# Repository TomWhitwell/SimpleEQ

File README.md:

# SimpleEQ  
Learn SMD soldering by building two channels of the kind of tone controls you’d find on an old hifi. 

Top channel = Baxandall EQ, treble/bass cut/boost   
Bottom channel = Tilt EQ  

No voltage control, but just enough range to push sounds into distortion. 

Works well in a feedback loop.

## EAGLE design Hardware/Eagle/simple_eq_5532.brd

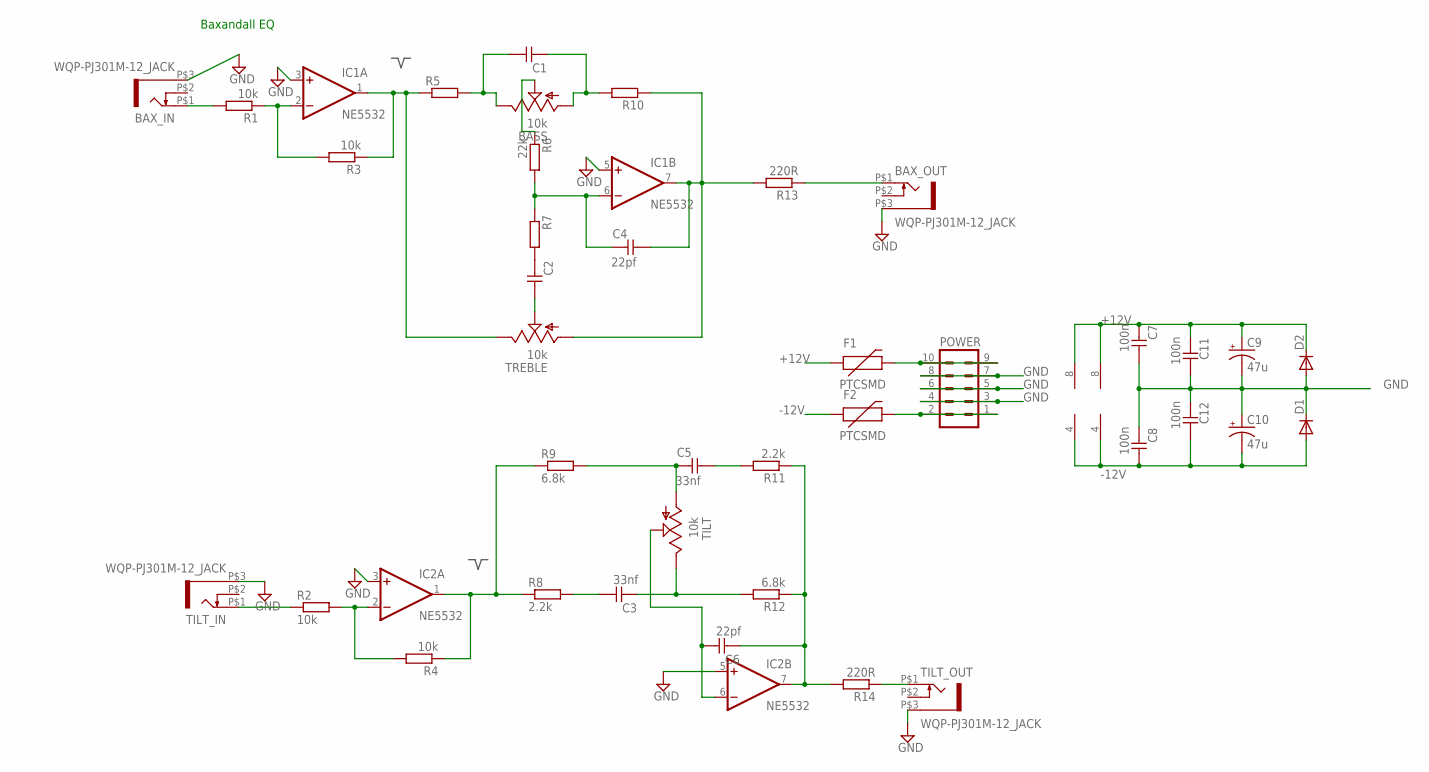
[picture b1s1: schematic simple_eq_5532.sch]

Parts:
BASS: 10k; EVUF
BAX_IN: WQP-PJ301M-12_JACK
BAX_OUT: WQP-PJ301M-12_JACK
C1, C2: C-EU0805_CAP; R0805
C3, C5: 33nf; R0805
C4, C6: 22pf; R0805
C7, C8, C11, C12: 100n; R0805
C9, C10: 47u; PANASONIC_D
D1, D2: DIODE-SOD123; SOD123
F1, F2: PTCSMD; PTC-1206
IC1, IC2: NE5532; SO08
POWER: 10_PIN_HEADER; MA05-2
R1, R2, R3, R4: 10k; R0805
R5, R7, R10: R-EU_R0805; R0805
R6: 22k; R0805
R8, R11: 2.2k; R0805
R9, R12: 6.8k; R0805
R13, R14: 220R; R0805
TILT: 10k; EVUF
TILT_IN: WQP-PJ301M-12_JACK
TILT_OUT: WQP-PJ301M-12_JACK
TREBLE: 10k; EVUF

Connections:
+12V: C7.2, C9.+, C11.2, D2.C, F1.1, IC1.8 (V+), IC2.8 (V+)
-12V: C8.1, C10.-, C12.1, D1.A, F2.1, IC1.4 (V-), IC2.4 (V-)
BAX1: C4.1, IC1.7 (OUT), R10.1, R13.2, TREBLE.1 (A)
BAX$1: BAX_IN.P$1 (2), R1.2
BAX$2: BAX_OUT.P$1 (2), R13.1
BAX$24: IC1.2 (-IN), R1.1, R3.2
BAX$26: C2.1, TREBLE.2 (S)
BAX$27: BASS.3 (E), C1.1, R5.2
BAX$28: BASS.1 (A), C1.2, R10.2
BAX$29: BASS.2 (S), R6.1
BAX$31: IC1.1 (OUT), R3.1, R5.1, TREBLE.3 (E)
BAX$32: C4.2, IC1.6 (-IN), R6.2, R7.1
GND: BAX_IN.P$3 (1), BAX_OUT.P$3 (1), C7.1, C8.2, C9.-, C10.+, C11.1, C12.2, D1.C, D2.A, IC1.3 (+IN), IC1.5 (+IN), IC2.3 (+IN), IC2.5 (+IN), POWER.3, POWER.4, POWER.5, POWER.6, POWER.7, POWER.8, TILT_IN.P$3 (1), TILT_OUT.P$3 (1)
unnamed: IC2.2 (-IN), R2.2, R4.2
unnamed: IC2.1 (OUT), R4.1, R8.1, R9.1
unnamed: R14.1, TILT_OUT.P$1 (2)
unnamed: R2.1, TILT_IN.P$1 (2)
unnamed: F1.2, POWER.9, POWER.10
unnamed: F2.2, POWER.1, POWER.2
unnamed: C3.1, R8.2
unnamed: C3.2, R12.2, TILT.3 (E)
unnamed: C5.2, R9.2, TILT.1 (A)
unnamed: C5.1, R11.2
unnamed: C6.1, IC2.6 (-IN), TILT.2 (S)
unnamed: C2.2, R7.2
TILT_OUT: C6.2, IC2.7 (OUT), R11.1, R12.1, R14.2

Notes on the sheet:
Baxandall EQ

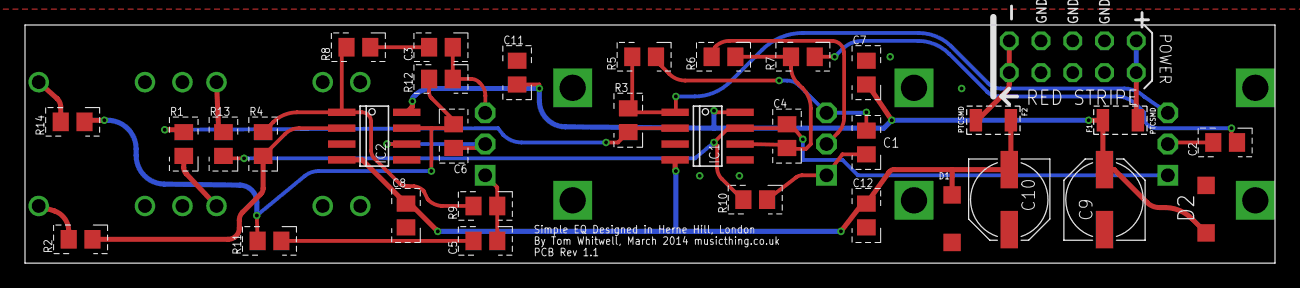
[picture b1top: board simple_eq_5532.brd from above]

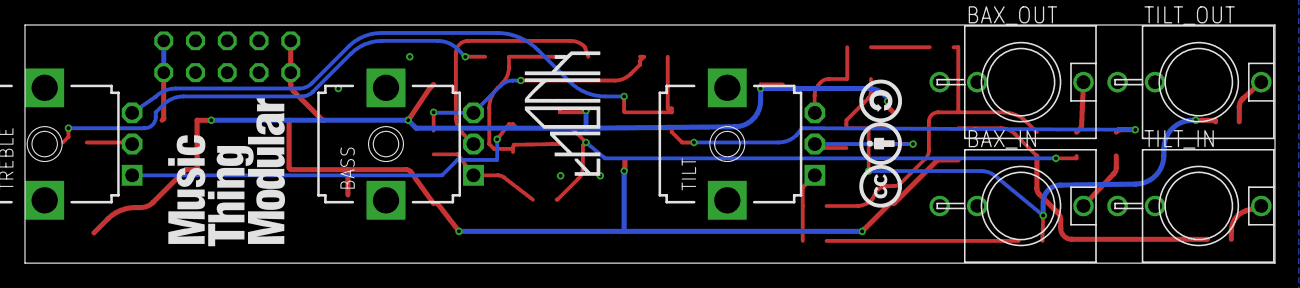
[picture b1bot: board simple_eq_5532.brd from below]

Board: 4 copper layers, 100.0 x 19.1 mm, 43 parts (10 on the bottom side), 26 nets.

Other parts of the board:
U$5: MTM_1CM
U$6: CC_1CM_SCREENPRINT
U$7: THONK_1CM_SCREENPRINT

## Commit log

2015-06-23 Initial bundle as first successful build
2015-06-23 Rev 1.1 updated Thonkiconn socket outlines

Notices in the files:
parts and their libraries:
SparkFun-PowerIC: Licensing: CC v3.0 Share-Alike You are welcome to use this library for commercial purposes.
